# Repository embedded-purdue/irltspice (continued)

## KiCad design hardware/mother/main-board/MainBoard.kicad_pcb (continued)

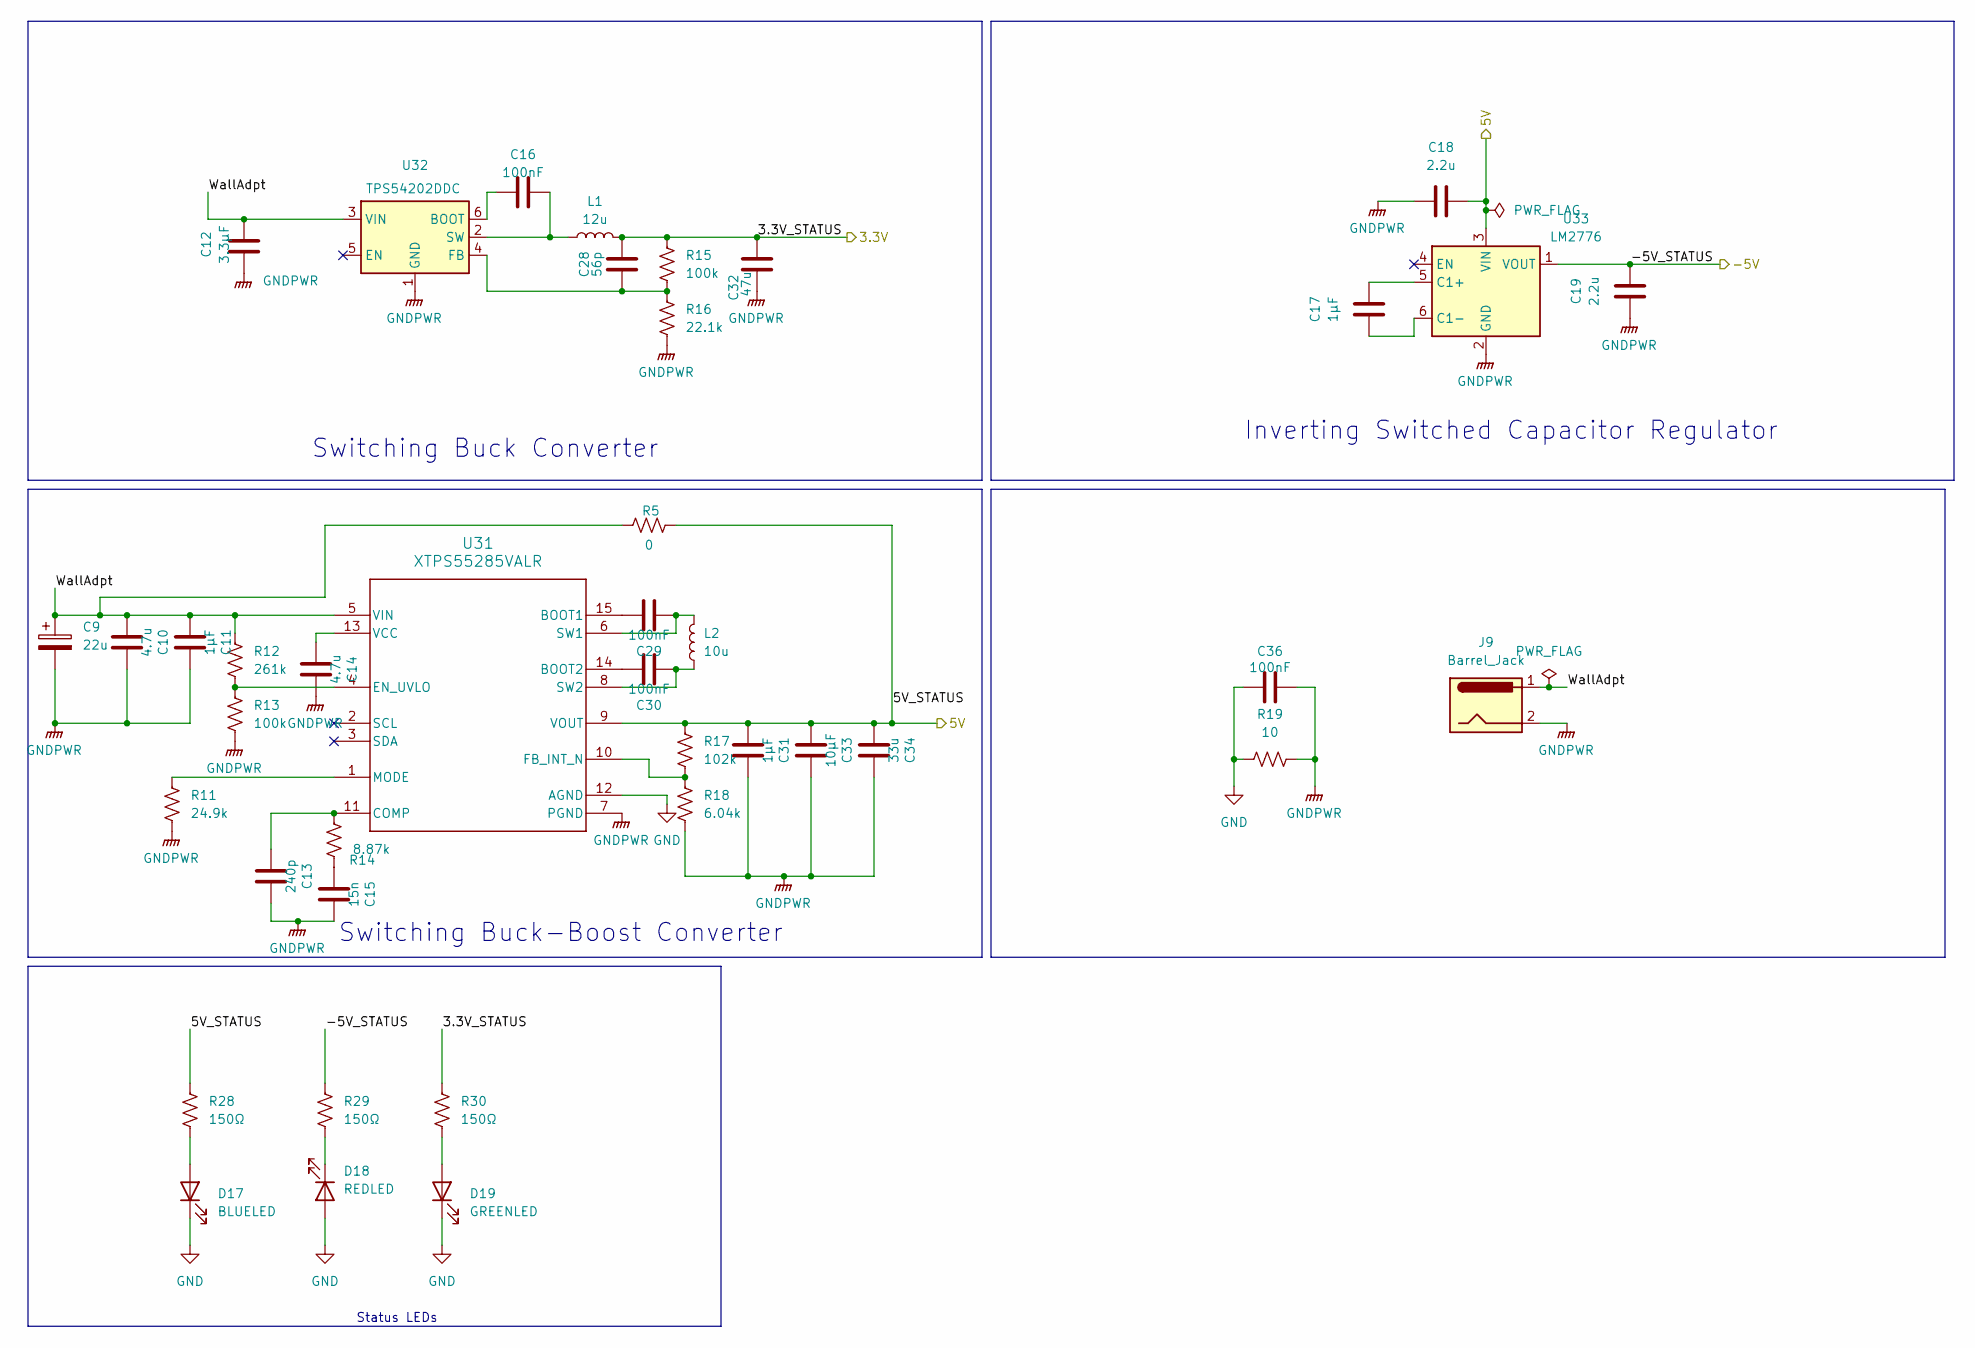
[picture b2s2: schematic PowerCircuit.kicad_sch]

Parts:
C9: 22u; CAP_EEFK_C_PAN
C10: 4.7u; C_1210_3225Metric_Pad1.33x2.70mm_HandSolder
C11, C17: 1µF; C_0603_1608Metric_Pad1.08x0.95mm_HandSolder
C12: 3.3µF; C_1210_3225Metric_Pad1.33x2.70mm_HandSolder
C13: 240p; C_0603_1608Metric_Pad1.08x0.95mm_HandSolder
C14: 4.7u; C_0603_1608Metric_Pad1.08x0.95mm_HandSolder
C15: 15n; C_0603_1608Metric_Pad1.08x0.95mm_HandSolder
C16: 100nF; C_0805_2012Metric_Pad1.18x1.45mm_HandSolder
C18, C19: 2.2u; C_0603_1608Metric_Pad1.08x0.95mm_HandSolder
C28: 56p; C_0603_1608Metric_Pad1.08x0.95mm_HandSolder
C29, C30, C36: 100nF; C_0603_1608Metric_Pad1.08x0.95mm_HandSolder
C31: 1µF; C_0201_0603Metric_Pad0.64x0.40mm_HandSolder
C32: 47u; C_0805_2012Metric_Pad1.18x1.45mm_HandSolder
C33: 10µF; C_1210_3225Metric_Pad1.33x2.70mm_HandSolder
C34: 33u; CP_EIA-3528-21_Kemet-B_HandSolder
D17: BLUELED; D_0805_2012Metric_Pad1.15x1.40mm_HandSolder
D18: REDLED; D_0805_2012Metric_Pad1.15x1.40mm_HandSolder
D19: GREENLED; D_0805_2012Metric_Pad1.15x1.40mm_HandSolder
J9: Barrel_Jack; BarrelJack_CUI_PJ-063AH_Horizontal
L1: 12u; IND_4532-WE-PD2_WRE-L
L2: 10u; L_Bourns_SRN6045TA
R5: 0; R_0603_1608Metric_Pad0.98x0.95mm_HandSolder
R11: 24.9k; R_0603_1608Metric_Pad0.98x0.95mm_HandSolder
R12: 261k; R_0603_1608Metric_Pad0.98x0.95mm_HandSolder
R13, R15: 100k; R_0603_1608Metric_Pad0.98x0.95mm_HandSolder
R14: 8.87k; R_0603_1608Metric_Pad0.98x0.95mm_HandSolder
R16: 22.1k; R_0603_1608Metric_Pad0.98x0.95mm_HandSolder
R17: 102k; R_0603_1608Metric_Pad0.98x0.95mm_HandSolder
R18: 6.04k; R_0603_1608Metric_Pad0.98x0.95mm_HandSolder
R19: 10; R_0603_1608Metric_Pad0.98x0.95mm_HandSolder
R28, R29, R30: 150Ω; R_0603_1608Metric_Pad0.98x0.95mm_HandSolder
U31: XTPS55285VALR; TPS55285
U32: TPS54202DDC; SOT-23-6
U33: LM2776; SOT-23-6

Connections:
/Power Supply/3.3V_STATUS: C28.2, C32.2, L1.2, R15.1, R30.1; also elsewhere on the board
/Power Supply/5V_STATUS: C18.2, C31.1, C33.1, C34.1, R5.2, R17.1, R28.1, U31.9 (VOUT), U33.3 (VIN); also elsewhere on the board
/Power Supply/-5V_STATUS: C19.2, R29.1, U33.1 (VOUT); also elsewhere on the board
/Power Supply/WallAdpt: C9.1, C10.1, C11.1, C12.2, J9.1, R5.1, R12.1, U31.5 (VIN), U32.3 (VIN)
GND: C36.1, D17.1 (K), D18.2 (A), D19.1 (K), R19.1, U31.12 (AGND); also elsewhere on the board
GNDPWR: C9.2, C10.2, C11.2, C12.1, C13.2, C14.2, C15.2, C18.1, C19.1, C31.2, C32.1, C33.2, C34.2, C36.2, J9.2, R11.2, R13.2, R16.2, R18.2, R19.2, U31.7 (PGND), U32.1 (GND), U33.2 (GND); also elsewhere on the board
unnamed: C15.1, R14.2
unnamed: D17.2 (A), R28.2
unnamed: D18.1 (K), R29.2
unnamed: D19.2 (A), R30.2
unnamed: C29.2, U31.15 (BOOT1)
unnamed: C30.2, U31.14 (BOOT2)
unnamed: C13.1, R14.1, U31.11 (COMP)
unnamed: R12.2, R13.1, U31.4 (EN_UVLO)
unnamed: R17.2, R18.1, U31.10 (FB_INT_N)
unnamed: R11.1, U31.1 (MODE)
unnamed: C29.1, L2.2, U31.6 (SW1)
unnamed: C30.1, L2.1, U31.8 (SW2)
unnamed: C14.1, U31.13 (VCC)
unnamed: C16.1, U32.6 (BOOT)
unnamed: C28.1, R15.2, R16.1, U32.4 (FB)
unnamed: C16.2, L1.1, U32.2 (SW)
unnamed: C17.2, U33.5 (C1+)
unnamed: C17.1, U33.6 (C1-)

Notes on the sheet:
Switching Buck Converter
Inverting Switched Capacitor Regulator
Status LEDs
Switching Buck-Boost Converter

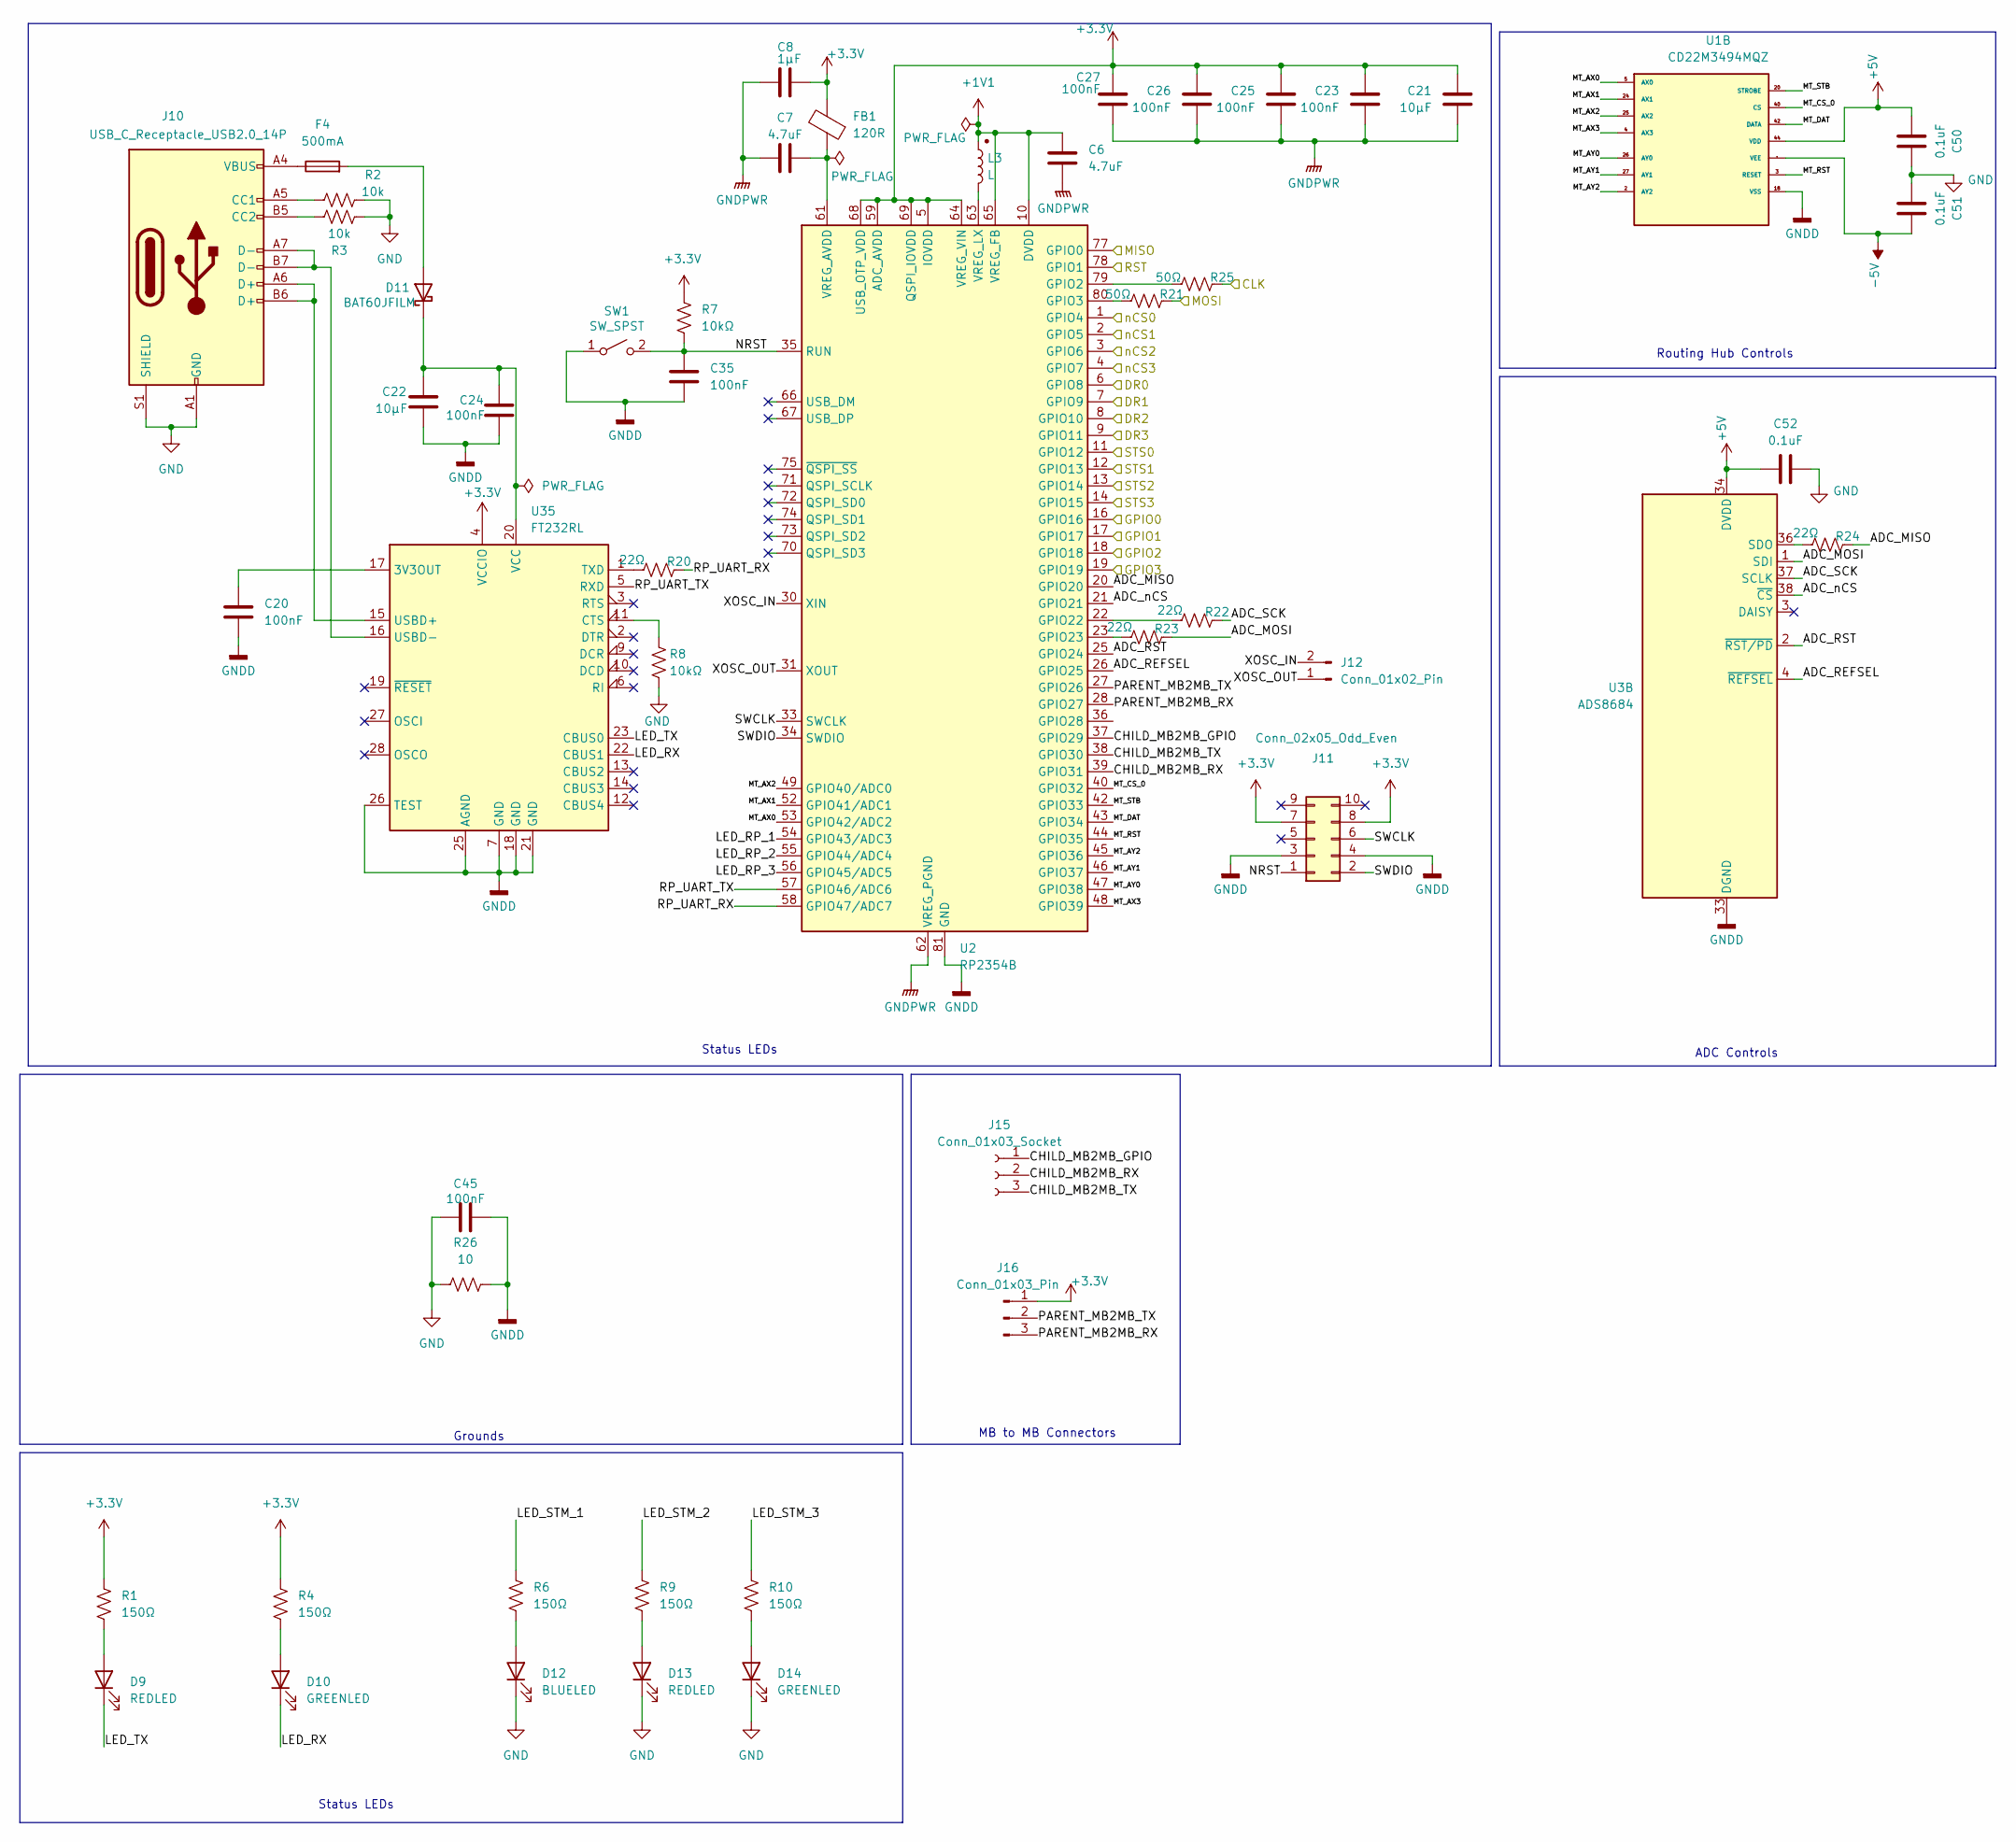
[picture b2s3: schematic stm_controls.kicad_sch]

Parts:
C6, C7: 4.7uF; C_0603_1608Metric_Pad1.08x0.95mm_HandSolder
C8: 1µF; C_0603_1608Metric_Pad1.08x0.95mm_HandSolder
C20, C23, C24, C25, C26, C27, C35: 100nF; C_0603_1608Metric_Pad1.08x0.95mm_HandSolder
C21, C22: 10µF; C_0603_1608Metric_Pad1.08x0.95mm_HandSolder
C45: 100nF; C_0402_1005Metric_Pad0.74x0.62mm_HandSolder
C50, C51, C52: 0.1uF; C_0603_1608Metric_Pad1.08x0.95mm_HandSolder
D9, D13: REDLED; D_0805_2012Metric_Pad1.15x1.40mm_HandSolder
D10, D14: GREENLED; D_0805_2012Metric_Pad1.15x1.40mm_HandSolder
D11: BAT60JFILM; D_SOD-323_HandSoldering
D12: BLUELED; D_0805_2012Metric_Pad1.15x1.40mm_HandSolder
F4: 500mA; Fuse_0603_1608Metric_Pad1.05x0.95mm_HandSolder
FB1: 120R; L_0603_1608Metric_Pad1.05x0.95mm_HandSolder
J10: USB_C_Receptacle_USB2.0_14P; USB_C_Receptacle_G-Switch_GT-USB-7010ASV
J11: Conn_02x05_Odd_Even; PinHeader_2x05_P2.54mm_Vertical
J12: Conn_01x02_Pin; PinSocket_1x02_P2.54mm_Vertical
J15: Conn_01x03_Socket
J16: Conn_01x03_Pin
L3: L; L_Abracon_AOTA-B201610S
R1, R4, R6, R9, R10: 150Ω; R_0603_1608Metric_Pad0.98x0.95mm_HandSolder
R2, R3: 10k; R_0603_1608Metric_Pad0.98x0.95mm_HandSolder
R7, R8: 10kΩ; R_0603_1608Metric_Pad0.98x0.95mm_HandSolder
R20, R22, R23, R24: 22Ω; R_0603_1608Metric_Pad0.98x0.95mm_HandSolder
R21, R25: 50Ω; R_0603_1608Metric_Pad0.98x0.95mm_HandSolder
R26: 10; R_0603_1608Metric_Pad0.98x0.95mm_HandSolder
SW1: SW_SPST; SW_SPST_SKQG_WithoutStem
U1: CD22M3494MQZ; PLCC44_16P66X16P66_INR-M; PARTREV September 2011
U2: RP2354B; QFN-80-1EP_10x10mm_P0.4mm_EP3.4x3.4mm
U3: ADS8684; TSSOP-38_4.4x9.7mm_P0.5mm
U35: FT232RL; SSOP-28_5.3x10.2mm_P0.65mm

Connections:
+1V1: C6.1, L3.1, U2.10 (DVDD), U2.32 (DVDD), U2.51 (DVDD), U2.65 (VREG_FB)
+3.3V: C8.1, C21.1, C23.1, C25.1, C26.1, C27.1, FB1.2, J11.7, J11.8, R1.1, R4.1, R7.1, U2.5 (IOVDD), U2.15 (IOVDD), U2.24 (IOVDD), U2.29 (IOVDD), U2.41 (IOVDD), U2.50 (IOVDD), U2.59 (ADC_AVDD), U2.60 (IOVDD), U2.64 (VREG_VIN), U2.68 (USB_OTP_VDD), U2.69 (QSPI_IOVDD), U2.76 (IOVDD), U35.4 (VCCIO); also elsewhere on the board
+5V: C50.1, C52.1, U1.44 (VDD), U3.34 (DVDD); also elsewhere on the board
-5V: C51.2, U1.22 (VEE); also elsewhere on the board
/DR0: U2.6 (GPIO8); also elsewhere on the board
/DR1: U2.7 (GPIO9); also elsewhere on the board
/DR2: U2.8 (GPIO10); also elsewhere on the board
/DR3: U2.9 (GPIO11); also elsewhere on the board
/GPIO0: U2.16 (GPIO16); also elsewhere on the board
/GPIO1: U2.17 (GPIO17); also elsewhere on the board
/GPIO2: U2.18 (GPIO18); also elsewhere on the board
/GPIO3: U2.19 (GPIO19); also elsewhere on the board
/MicroController/ADC_MISO: R24.2, U2.20 (GPIO20)
/MicroController/ADC_MOSI: R23.2, U3.1 (SDI)
/MicroController/ADC_REFSEL: U2.26 (GPIO25), U3.4 (~REFSEL)
/MicroController/ADC_RST: U2.25 (GPIO24), U3.2 (~RST/PD)
/MicroController/ADC_SCK: R22.2, U3.37 (SCLK)
/MicroController/ADC_nCS: U2.21 (GPIO21), U3.38 (~CS)
/MicroController/CHILD_MB2MB_GPIO: J15.1, U2.37 (GPIO29)
/MicroController/CHILD_MB2MB_RX: J15.2, U2.39 (GPIO31)
/MicroController/CHILD_MB2MB_TX: J15.3, U2.38 (GPIO30)
/MicroController/LED_RP_1: U2.54 (GPIO43/ADC3)
/MicroController/LED_RP_2: U2.55 (GPIO44/ADC4)
/MicroController/LED_RP_3: U2.56 (GPIO45/ADC5)
/MicroController/LED_RX: D10.1 (K), U35.22 (CBUS1)
/MicroController/LED_STM_1: R6.1
/MicroController/LED_STM_2: R9.1
/MicroController/LED_STM_3: R10.1
/MicroController/LED_TX: D9.1 (K), U35.23 (CBUS0)
/MicroController/MT_AX0: U1.5 (AX0), U2.53 (GPIO42/ADC2)
/MicroController/MT_AX1: U1.24 (AX1), U2.52 (GPIO41/ADC1)
/MicroController/MT_AX2: U1.25 (AX2), U2.49 (GPIO40/ADC0)
/MicroController/MT_AX3: U1.4 (AX3), U2.48 (GPIO39)
/MicroController/MT_AY0: U1.26 (AY0), U2.47 (GPIO38)
/MicroController/MT_AY1: U1.27 (AY1), U2.46 (GPIO37)
/MicroController/MT_AY2: U1.2 (AY2), U2.45 (GPIO36)
/MicroController/MT_CS_0: U1.40 (CS), U2.40 (GPIO32)
/MicroController/MT_DAT: U1.42 (DATA), U2.43 (GPIO34)
/MicroController/MT_RST: U1.3 (RESET), U2.44 (GPIO35)
/MicroController/MT_STB: U1.20 (STROBE), U2.42 (GPIO33)
/MicroController/NRST: C35.1, J11.1, R7.2, SW1.2 (B), U2.35 (RUN)
/MicroController/PARENT_MB2MB_RX: J16.3, U2.28 (GPIO27)
/MicroController/PARENT_MB2MB_TX: J16.2, U2.27 (GPIO26)
/MicroController/RP_UART_RX: R20.2, U2.58 (GPIO47/ADC7)
/MicroController/RP_UART_TX: U2.57 (GPIO46/ADC6), U35.5 (RXD)
/MicroController/SWCLK: J11.6, U2.33 (SWCLK)
/MicroController/SWDIO: J11.2, U2.34 (SWDIO)
/MicroController/XOSC_IN: J12.2, U2.30 (XIN)
/MicroController/XOSC_OUT: J12.1, U2.31 (XOUT)
/STD_CLK: R25.2; also elsewhere on the board
/STD_MISO: U2.77 (GPIO0); also elsewhere on the board
/STD_MOSI: R21.2; also elsewhere on the board
/STD_RST: U2.78 (GPIO1); also elsewhere on the board
/STS0: U2.11 (GPIO12); also elsewhere on the board
/STS1: U2.12 (GPIO13); also elsewhere on the board
/STS2: U2.13 (GPIO14); also elsewhere on the board
/STS3: U2.14 (GPIO15); also elsewhere on the board
/nCS0: U2.1 (GPIO4); also elsewhere on the board
/nCS1: U2.2 (GPIO5); also elsewhere on the board
/nCS2: U2.3 (GPIO6); also elsewhere on the board
/nCS3: U2.4 (GPIO7); also elsewhere on the board
GND: C45.1, C50.2, C51.1, C52.2, D12.1 (K), D13.1 (K), D14.1 (K), J10.A1 (GND), J10.A12 (GND), J10.B1 (GND), J10.B12 (GND), J10.S1 (SHIELD), R2.2, R3.2, R8.2, R26.1; also elsewhere on the board
GNDD: C20.2, C22.2, C24.2, C35.2, C45.2, J11.3, J11.4, R26.2, SW1.1 (A), U1.18 (VSS), U2.81 (GND), U3.33 (DGND), U35.7 (GND), U35.18 (GND), U35.21 (GND), U35.25 (AGND), U35.26 (TEST); also elsewhere on the board
GNDPWR: C6.2, C7.2, C8.2, C21.2, C23.2, C25.2, C26.2, C27.2, U2.62 (VREG_PGND); also elsewhere on the board
unnamed: D9.2 (A), R1.2
unnamed: D10.2 (A), R4.2
unnamed: D11.2 (A), F4.2
unnamed: C22.1, C24.1, D11.1 (K), U35.20 (VCC)
unnamed: D12.2 (A), R6.2
unnamed: D13.2 (A), R9.2
unnamed: D14.2 (A), R10.2
unnamed: F4.1, J10.A4 (VBUS), J10.A9 (VBUS), J10.B4 (VBUS), J10.B9 (VBUS)
unnamed: J10.A5 (CC1), R2.1
unnamed: J10.B5 (CC2), R3.1
unnamed: R25.1, U2.79 (GPIO2)
unnamed: R21.1, U2.80 (GPIO3)
unnamed: R22.1, U2.22 (GPIO22)
unnamed: R23.1, U2.23 (GPIO23)
unnamed: C7.1, FB1.1, U2.61 (VREG_AVDD)
unnamed: L3.2, U2.63 (VREG_LX)
unnamed: U3.28 (AGND), U3.29 (AGND), U3.31 (AGND), U3.32 (AGND)
unnamed: R24.1, U3.36 (SDO)
unnamed: C20.1, U35.17 (3V3OUT)
unnamed: R8.1, U35.11 (CTS)
unnamed: R20.1, U35.1 (TXD)
unnamed: J10.A6 (D+), J10.B6 (D+), U35.15 (USBD+)
unnamed: J10.A7 (D-), J10.B7 (D-), U35.16 (USBD-)

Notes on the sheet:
Status LEDs
MB to MB Connectors
Routing Hub Controls
ADC Controls
Grounds

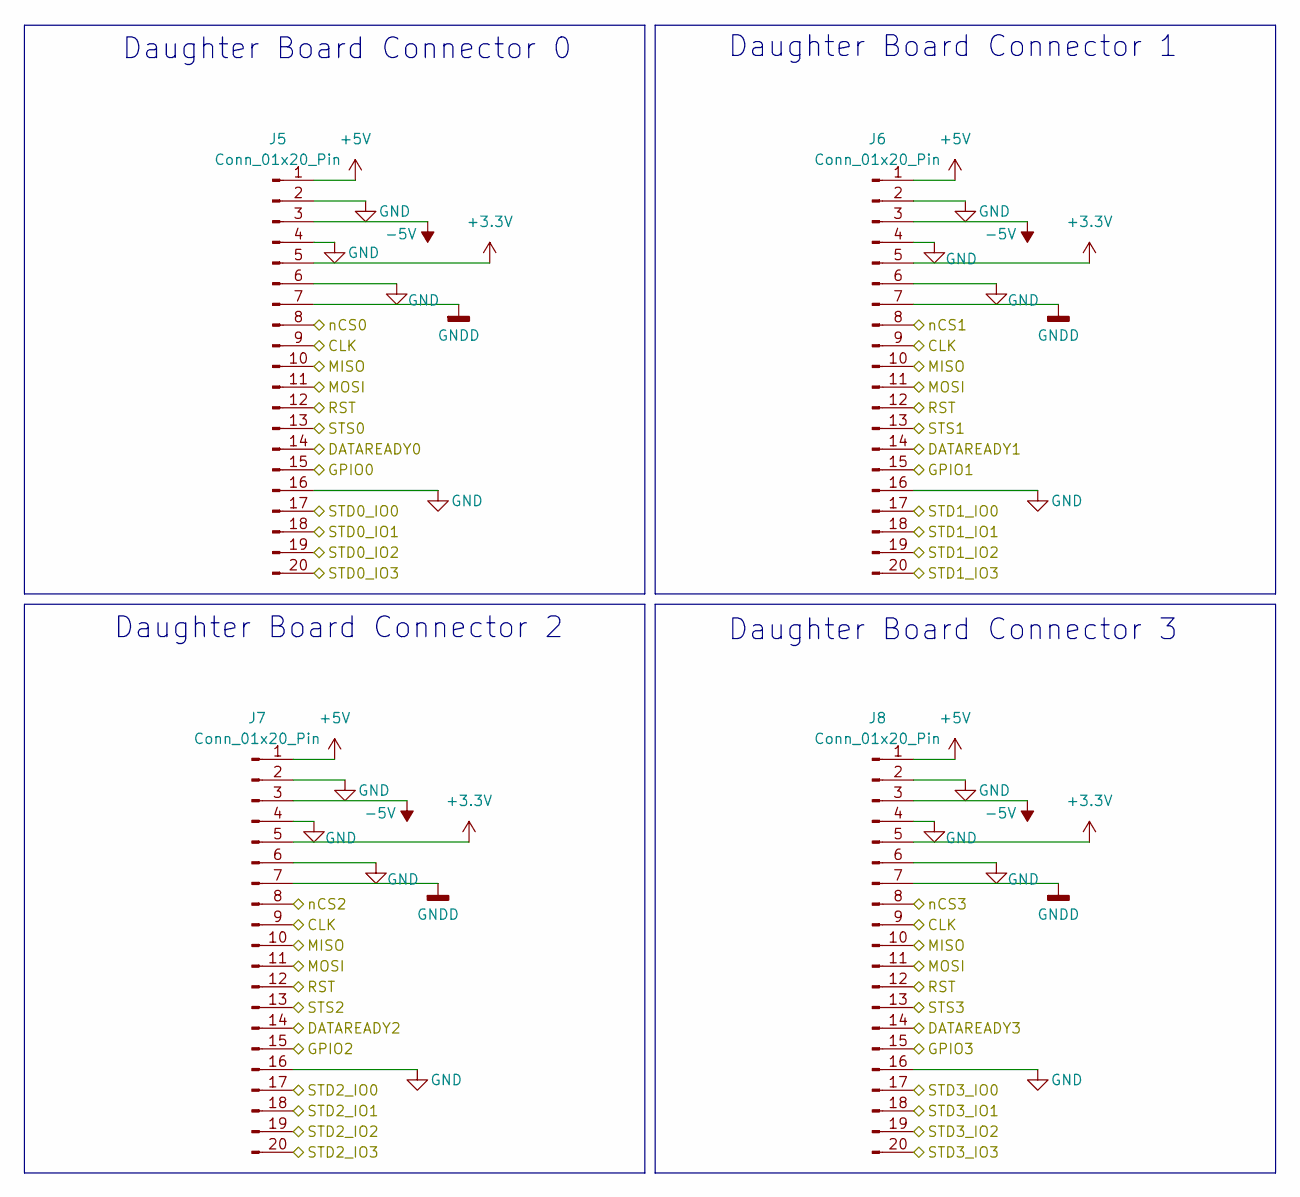
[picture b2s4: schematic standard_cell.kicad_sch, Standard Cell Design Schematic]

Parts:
J5, J6, J7, J8: Conn_01x20_Pin; PinSocket_2x10_P2.54mm_Vertical

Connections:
+3.3V: J5.5, J6.5, J7.5, J8.5; also elsewhere on the board
+5V: J5.1, J6.1, J7.1, J8.1; also elsewhere on the board
-5V: J5.3, J6.3, J7.3, J8.3; also elsewhere on the board
/DR0: J5.14; also elsewhere on the board
/DR1: J6.14; also elsewhere on the board
/DR2: J7.14; also elsewhere on the board
/DR3: J8.14; also elsewhere on the board
/GPIO0: J5.15; also elsewhere on the board
/GPIO1: J6.15; also elsewhere on the board
/GPIO2: J7.15; also elsewhere on the board
/GPIO3: J8.15; also elsewhere on the board
/STD0_IO0: J5.17
/STD0_IO1: J5.18; also elsewhere on the board
/STD0_IO2: J5.19; also elsewhere on the board
/STD0_IO3: J5.20; also elsewhere on the board
/STD1_IO0: J6.17; also elsewhere on the board
/STD1_IO1: J6.18; also elsewhere on the board
/STD1_IO2: J6.19; also elsewhere on the board
/STD1_IO3: J6.20; also elsewhere on the board
/STD2_IO0: J7.17; also elsewhere on the board
/STD2_IO1: J7.18; also elsewhere on the board
/STD2_IO2: J7.19; also elsewhere on the board
/STD2_IO3: J7.20; also elsewhere on the board
/STD3_IO0: J8.17; also elsewhere on the board
/STD3_IO1: J8.18; also elsewhere on the board
/STD3_IO2: J8.19; also elsewhere on the board
/STD3_IO3: J8.20; also elsewhere on the board
/STD_CLK: J5.9, J6.9, J7.9, J8.9; also elsewhere on the board
/STD_MISO: J5.10, J6.10, J7.10, J8.10; also elsewhere on the board
/STD_MOSI: J5.11, J6.11, J7.11, J8.11; also elsewhere on the board
/STD_RST: J5.12, J6.12, J7.12, J8.12; also elsewhere on the board
/STS0: J5.13; also elsewhere on the board
/STS1: J6.13; also elsewhere on the board
/STS2: J7.13; also elsewhere on the board
/STS3: J8.13; also elsewhere on the board
/nCS0: J5.8; also elsewhere on the board
/nCS1: J6.8; also elsewhere on the board
/nCS2: J7.8; also elsewhere on the board
/nCS3: J8.8; also elsewhere on the board
GND: J5.2, J5.4, J5.6, J5.16, J6.2, J6.4, J6.6, J6.16, J7.2, J7.4, J7.6, J7.16, J8.2, J8.4, J8.6, J8.16; also elsewhere on the board
GNDD: J5.7, J6.7, J7.7, J8.7; also elsewhere on the board

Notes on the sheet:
Daughter Board Connector 3
Daughter Board Connector 1
Daughter Board Connector 0
Daughter Board Connector 2

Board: 4 copper layers, 120 parts (5 on the bottom side), 123 nets, no tracks yet.

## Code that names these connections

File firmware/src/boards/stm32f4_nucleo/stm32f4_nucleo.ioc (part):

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Mcu.Name=STM32F446R(C-E)Tx
Mcu.Package=LQFP64
Mcu.UserName=STM32F446RETx
PA4.Mode=NSS_Signal_Hard_Input
PA4.Signal=SPI1_NSS
PA5.GPIOParameters=GPIO_Label
PA5.GPIO_Label=LED
PA5.Signal=GPIO_Output
PA6.Mode=Full_Duplex_Slave
PA6.Signal=SPI1_MISO
PA7.Mode=Full_Duplex_Slave
PA7.Signal=SPI1_MOSI
PA8.GPIOParameters=GPIO_Label
PA8.GPIO_Label=DATA_READY
PA8.Signal=GPIO_Output
PB3.Mode=Full_Duplex_Slave
PB3.Signal=SPI1_SCK
board=custom
